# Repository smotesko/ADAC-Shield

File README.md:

ADAC — ADC/DAC Arduino Shield. This is work in progress, nothing was tested or even finished yet.

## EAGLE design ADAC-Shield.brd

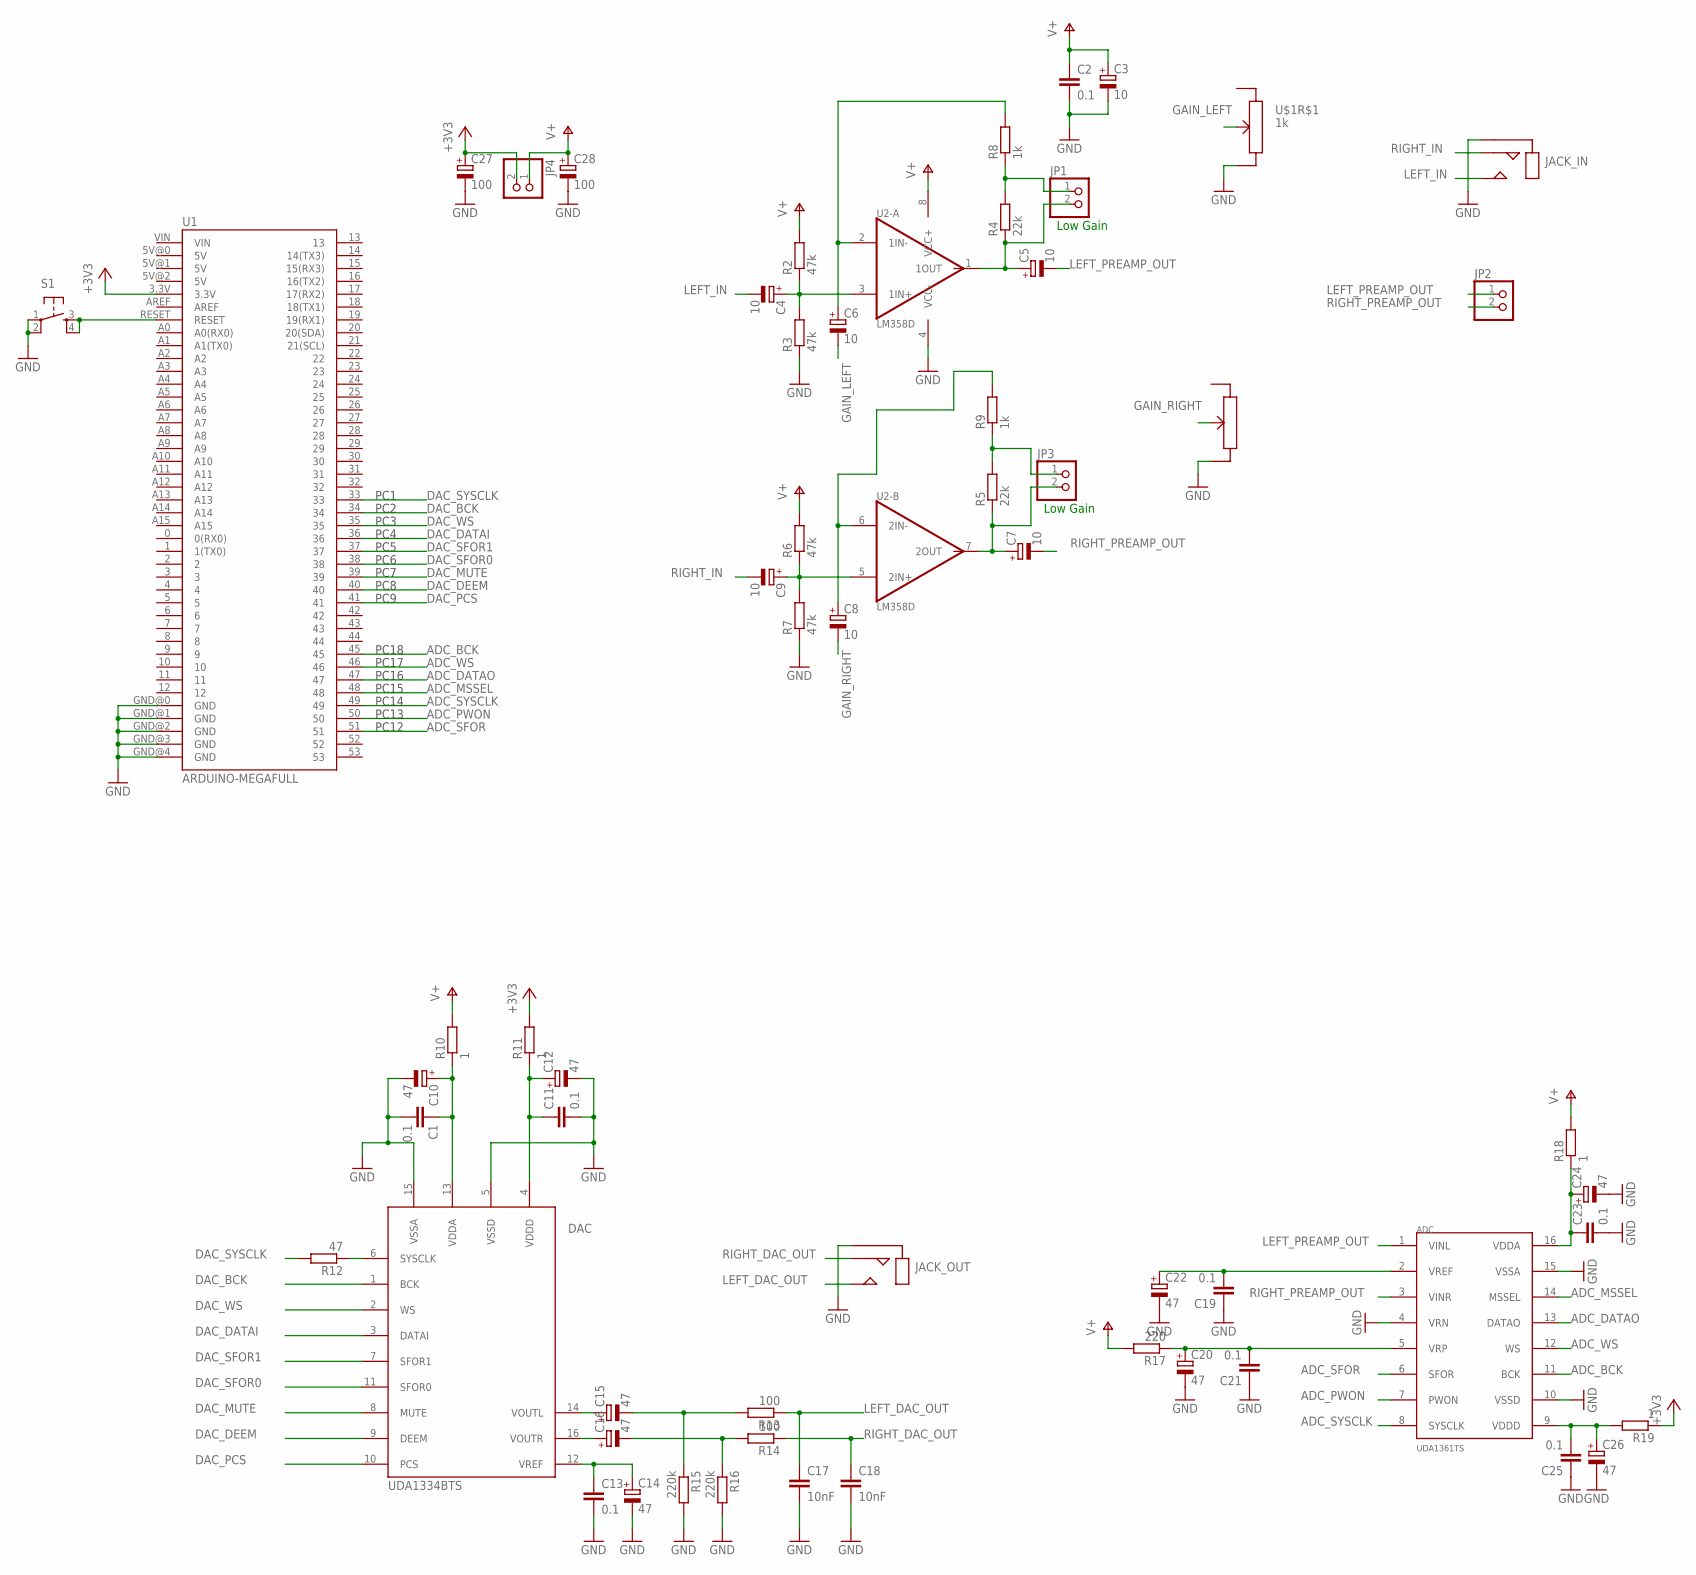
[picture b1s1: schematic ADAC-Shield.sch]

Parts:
ADC: UDA1361TS; SSOP16
C1, C2, C11, C13, C19, C21, C23, C25: 0.1; C0805
C3, C4, C5, C6, C7, C8, C9: 10; PANASONIC_A
C10, C12, C14, C15, C16, C20, C22, C24, C26: 47; PANASONIC_A
C17, C18: 10nF; C0805
C27, C28: 100; PANASONIC_B
DAC: UDA1334BTS; SSOP16
JACK_IN: ST-11M-0
JACK_OUT: ST-11M-0
JP1, JP2, JP3, JP4: PINHD-1X2; 1X02
R2, R3, R6, R7: 47k; R0805
R4, R5: 22k; R0805
R8, R9: 1k; R0805
R10, R11, R18, R19: 1; R0805
R12: 47; R0805
R13, R14: 100; R0805
R15, R16: 220k; R0805
R17: 220; R0805
S1: TAC_SWITCHSMD; TACTILE_SWITCH_SMD
U1: ARDUINO-MEGAFULL; ARDUINO_MEGA
U2: LM358D; ANDREW/B37Z6
U$1: 1k; POT_DUAL_R16

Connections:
+3V3: C27.+, JP4.2, R11.2, R19.1, U1.3.3V
ADC_BCK: ADC.11 (BCK), U1.45
ADC_DATAO: ADC.13 (DATAO), U1.47
ADC_MSSEL: ADC.14 (MSSEL), U1.48
ADC_PWON: ADC.7 (PWON), U1.50
ADC_SFOR: ADC.6 (SFOR), U1.51
ADC_SYSCLK: ADC.8 (SYSCLK), U1.49
ADC_WS: ADC.12 (WS), U1.46
DAC_BCK: DAC.1 (BCK), U1.34
DAC_DATAI: DAC.3 (DATAI), U1.36
DAC_DEEM: DAC.9 (DEEM), U1.40
DAC_MUTE: DAC.8 (MUTE), U1.39
DAC_PCS: DAC.10 (PCS), U1.41
DAC_SFOR0: DAC.11 (SFOR0), U1.38
DAC_SFOR1: DAC.7 (SFOR1), U1.37
DAC_SYSCLK: R12.2, U1.33
DAC_WS: DAC.2 (WS), U1.35
GAIN_LEFT: C6.-, U$1.TRIMMER
GAIN_RIGHT: C8.-, U$1.TRIMMER2
GND: ADC.4 (VRN), ADC.10 (VSSD), ADC.15 (VSSA), C1.2, C2.2, C3.-, C10.-, C11.2, C12.-, C13.2, C14.-, C17.2, C18.2, C19.1, C20.-, C21.1, C22.-, C23.2, C24.-, C25.1, C26.-, C27.-, C28.-, DAC.5 (VSSD), DAC.15 (VSSA), JACK_IN.SLEEVE, JACK_OUT.SLEEVE, R3.1, R7.1, R15.2, R16.2, S1.1, S1.2, U1.GND@0 (GND), U1.GND@1 (GND), U1.GND@2 (GND), U1.GND@3 (GND), U1.GND@4 (GND), U2.4 (VCC-), U$1.BOTTOM, U$1.BOTTOM2
LEFT_DAC_OUT: C17.1, JACK_OUT.TIP, R13.1
LEFT_IN: C4.-, JACK_IN.TIP
LEFT_PREAMP_OUT: ADC.1 (VINL), C5.-, JP2.1
unnamed: C4.+, R2.1, R3.2, U2.3 (1IN+)
unnamed: C5.+, JP1.2, R4.1, U2.1 (1OUT)
unnamed: S1.3, S1.4, U1.RESET
unnamed: C6.+, R8.2, U2.2 (1IN-)
unnamed: C7.+, JP3.2, R5.1, U2.7 (2OUT)
unnamed: C11.1, C12.+, DAC.4 (VDDD), R11.1
unnamed: C8.+, R9.2, U2.6 (2IN-)
unnamed: C9.+, R6.1, R7.2, U2.5 (2IN+)
unnamed: JP1.1, R4.2, R8.1
unnamed: C1.1, C10.+, DAC.13 (VDDA), R10.1
unnamed: JP3.1, R5.2, R9.1
unnamed: DAC.6 (SYSCLK), R12.1
unnamed: C13.1, C14.+, DAC.12 (VREF)
unnamed: C15.+, DAC.14 (VOUTL)
unnamed: C16.+, DAC.16 (VOUTR)
unnamed: C15.-, R13.2, R15.1
unnamed: C16.-, R14.2, R16.1
unnamed: ADC.2 (VREF), C19.2, C22.+
unnamed: ADC.5 (VRP), C20.+, C21.2, R17.1
unnamed: ADC.16 (VDDA), C23.1, C24.+, R18.1
unnamed: ADC.9 (VDDD), C25.2, C26.+, R19.2
RIGHT_DAC_OUT: C18.1, JACK_OUT.RING, R14.1
RIGHT_IN: C9.-, JACK_IN.RING
RIGHT_PREAMP_OUT: ADC.3 (VINR), C7.-, JP2.2
V+: C2.1, C3.+, C28.+, JP4.1, R2.2, R6.2, R10.2, R17.2, R18.2, U2.8 (VCC+)

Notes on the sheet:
Low Gain
PC1
PC2
PC3
PC4
PC5
PC6
PC7
PC8
PC9
PC12
PC13
PC14
PC15
PC16
PC17
PC18

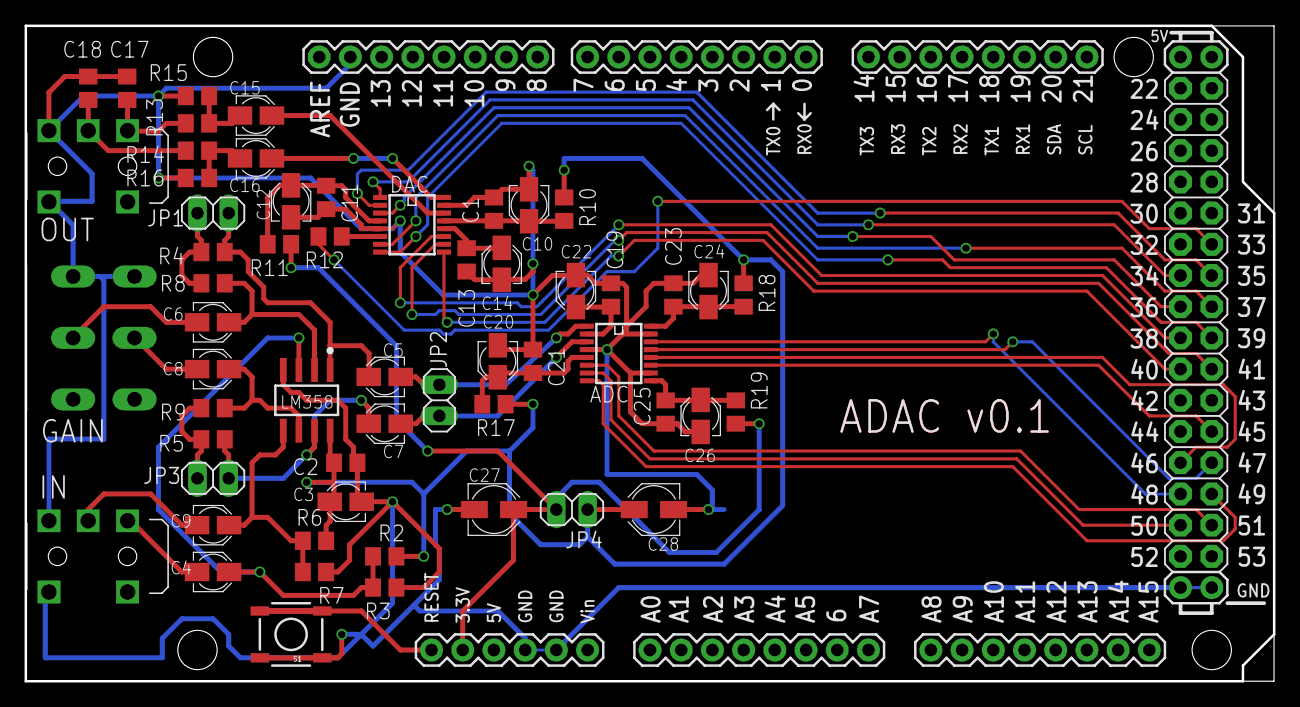
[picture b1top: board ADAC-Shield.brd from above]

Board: 2 copper layers, 101.6 x 53.3 mm, 58 parts (0 on the bottom side), 48 nets.

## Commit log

2014-03-18 Schematic finished. Started designing a PCB. Added schematic image
2014-03-18 Some progress in PCB layout
2014-03-19 PCB layout almost done
2014-03-22 Board layout finished for v0.1
2014-03-22 Updated the schematic image
2014-03-25 Small board fixes
2014-03-25 Increased isolation of the ground polygon
2014-03-25 Removed that shopping list

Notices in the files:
parts and their libraries:
SparkFun-Electromechanical: Licensing: Creative Commons ShareAlike 4.0 International - https://creativecommons.org/licenses/by-sa/4.0
